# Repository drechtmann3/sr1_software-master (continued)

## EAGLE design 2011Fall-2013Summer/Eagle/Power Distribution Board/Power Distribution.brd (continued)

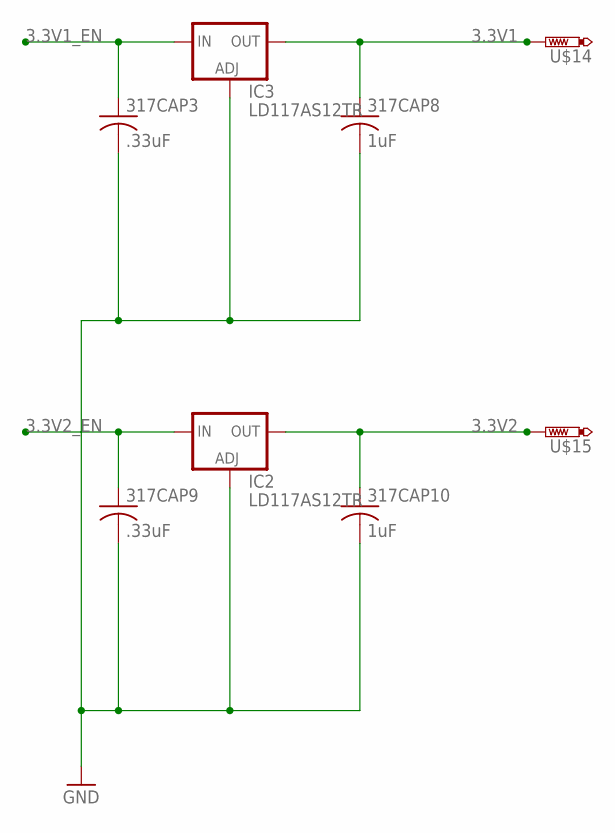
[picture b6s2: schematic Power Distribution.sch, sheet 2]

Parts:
317CAP3, 317CAP9: .33uF; C1206
317CAP8, 317CAP10: 1uF; C1206
IC2, IC3: LD117AS12TR; SOT223
U$14, U$15: TESTPAD-20MIL; 20MIL

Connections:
3.3V1: 317CAP8.1, IC3.4 (OUT), U$14.P$1; also elsewhere on the board
3.3V1_EN: 317CAP3.1, IC3.3 (IN); also elsewhere on the board
3.3V2: 317CAP10.1, IC2.4 (OUT), U$15.P$1; also elsewhere on the board
3.3V2_EN: 317CAP9.1, IC2.3 (IN); also elsewhere on the board
GND: 317CAP3.2, 317CAP8.2, 317CAP9.2, 317CAP10.2, IC2.1 (ADJ), IC3.1 (ADJ); also elsewhere on the board

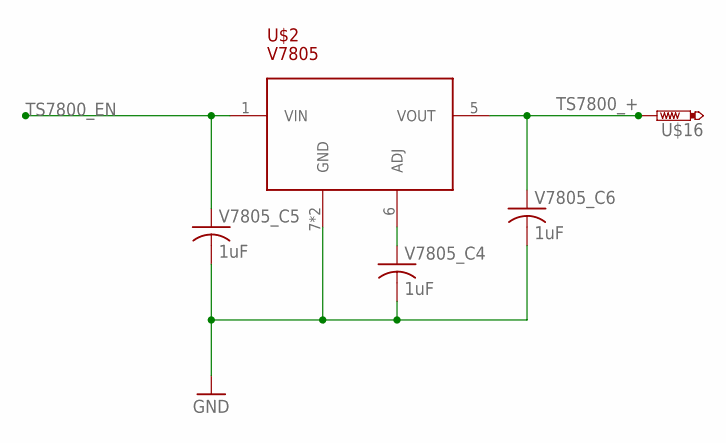
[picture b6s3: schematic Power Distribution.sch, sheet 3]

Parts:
U$2: V7805
U$16: TESTPAD-20MIL; 20MIL
V7805_C4, V7805_C5, V7805_C6: 1uF; C1206

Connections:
GND: U$2.7 (GND), U$2.9 (GND), V7805_C4.2, V7805_C5.2, V7805_C6.2; also elsewhere on the board
unnamed: U$2.6 (ADJ), V7805_C4.1
TS7800_+: U$2.5 (VOUT), U$16.P$1, V7805_C6.1; also elsewhere on the board
TS7800_EN: U$2.1 (VIN), V7805_C5.1; also elsewhere on the board

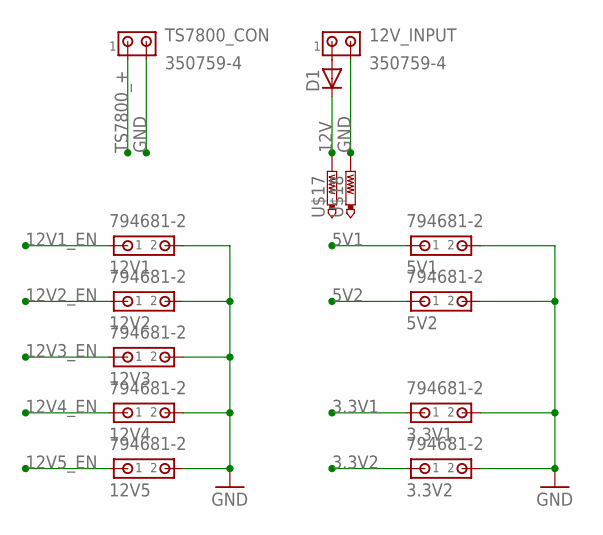
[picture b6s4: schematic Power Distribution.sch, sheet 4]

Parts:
3.3V1, 3.3V2, 5V1, 5V2, 12V1, 12V2, 12V3, 12V4, 12V5: 794681-2
12V_INPUT: 350759-4
D1: DIODE-SOD123; SOD123
TS7800_CON: 350759-4
U$17, U$18: TESTPAD-20MIL; 20MIL

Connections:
3.3V1: 3.3V1.1; also elsewhere on the board
3.3V2: 3.3V2.1; also elsewhere on the board
5V1: 5V1.1; also elsewhere on the board
5V2: 5V2.1; also elsewhere on the board
12V: D1.C, U$17.P$1; also elsewhere on the board
12V1_EN: 12V1.1; also elsewhere on the board
12V2_EN: 12V2.1; also elsewhere on the board
12V3_EN: 12V3.1; also elsewhere on the board
12V4_EN: 12V4.1; also elsewhere on the board
12V5_EN: 12V5.1; also elsewhere on the board
GND: 3.3V1.2, 3.3V2.2, 5V1.2, 5V2.2, 12V1.2, 12V2.2, 12V3.2, 12V4.2, 12V5.2, 12V_INPUT.2, TS7800_CON.2, U$18.P$1; also elsewhere on the board
unnamed: 12V_INPUT.1, D1.A
TS7800_+: TS7800_CON.1; also elsewhere on the board

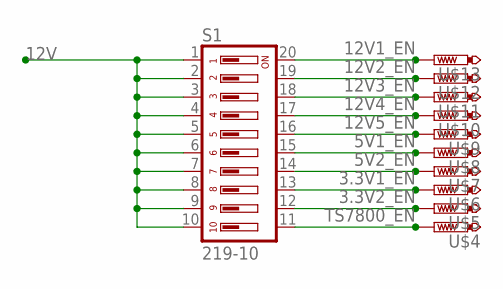
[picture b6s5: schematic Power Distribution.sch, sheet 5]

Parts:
S1: 219-10; CTS-219-10
U$4, U$5, U$6, U$7, U$8, U$9, U$10, U$11, U$12, U$13: TESTPAD-20MIL; 20MIL

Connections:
3.3V1_EN: S1.13, U$6.P$1; also elsewhere on the board
3.3V2_EN: S1.12, U$5.P$1; also elsewhere on the board
5V1_EN: S1.15, U$8.P$1; also elsewhere on the board
5V2_EN: S1.14, U$7.P$1; also elsewhere on the board
12V: S1.1, S1.2, S1.3, S1.4, S1.5, S1.6, S1.7, S1.8, S1.9, S1.10; also elsewhere on the board
12V1_EN: S1.20, U$13.P$1; also elsewhere on the board
12V2_EN: S1.19, U$12.P$1; also elsewhere on the board
12V3_EN: S1.18, U$11.P$1; also elsewhere on the board
12V4_EN: S1.17, U$10.P$1; also elsewhere on the board
12V5_EN: S1.16, U$9.P$1; also elsewhere on the board
TS7800_EN: S1.11, U$4.P$1; also elsewhere on the board

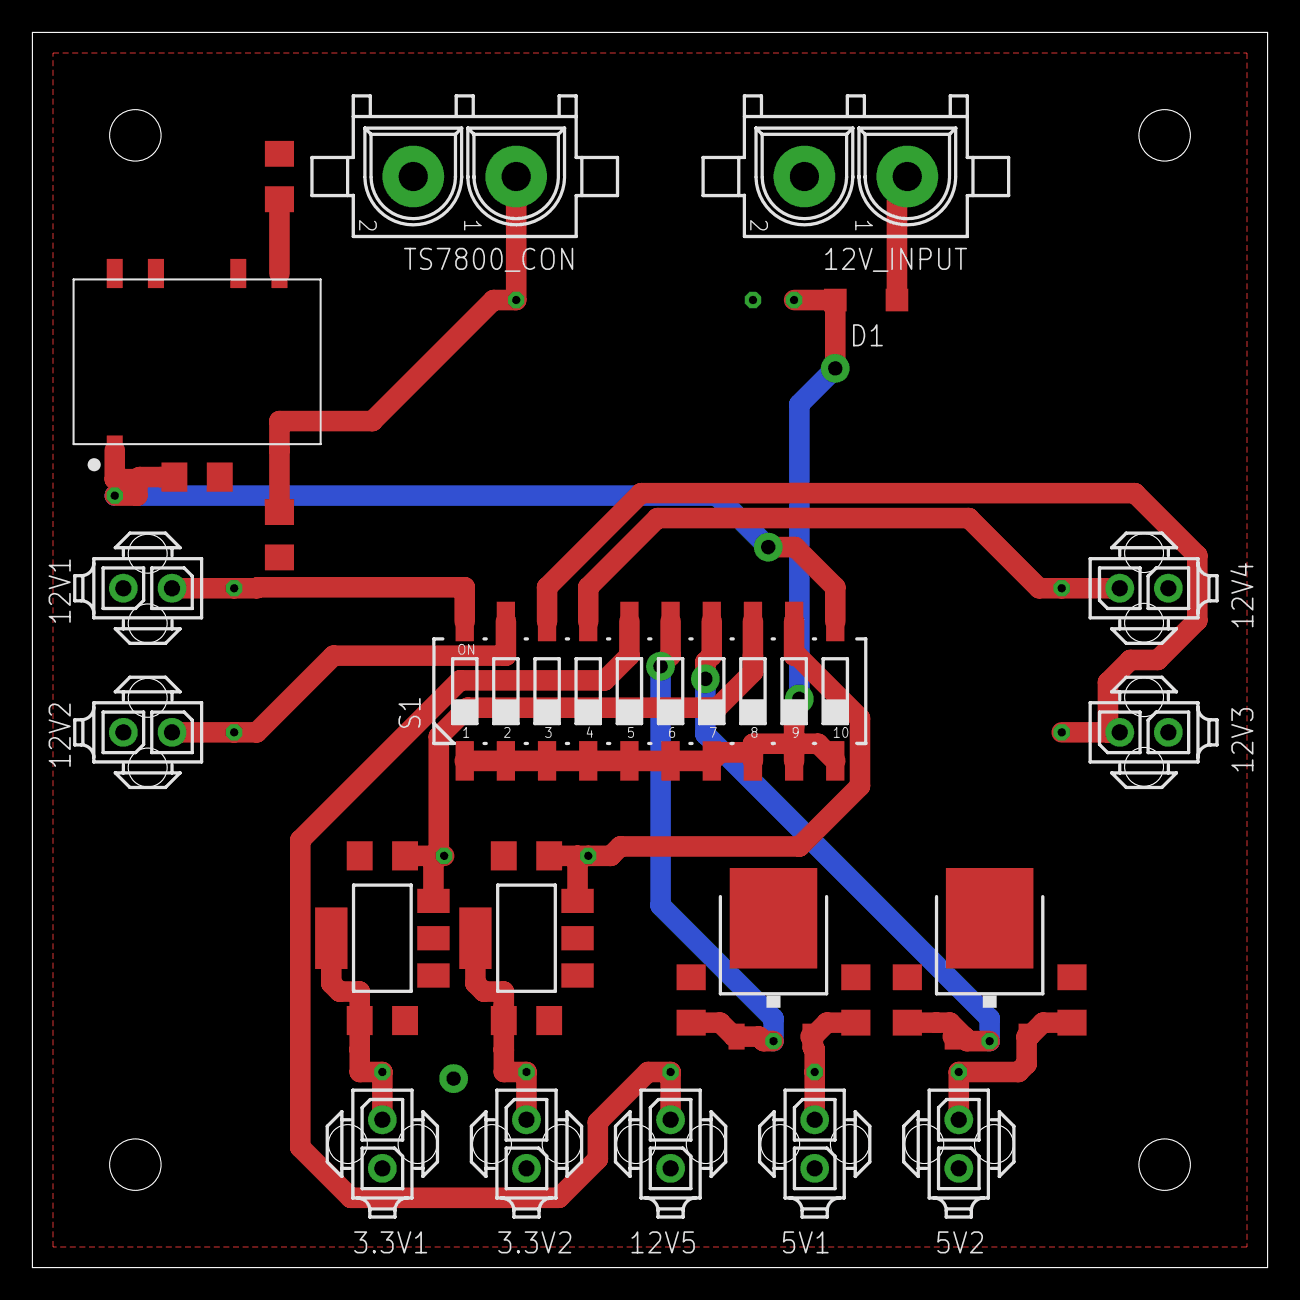
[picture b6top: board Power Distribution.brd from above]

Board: 2 copper layers, 76.2 x 76.2 mm, 46 parts (0 on the bottom side), 19 nets.

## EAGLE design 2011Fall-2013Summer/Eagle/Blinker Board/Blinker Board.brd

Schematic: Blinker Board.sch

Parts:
12V: TESTPAD-20MIL; 20MIL
B: TESTPAD-20MIL; 20MIL
BC: TESTPAD-20MIL; 20MIL
BL: TESTPAD-20MIL; 20MIL
BLC: TESTPAD-20MIL; 20MIL
BLINKER-L1, BLINKER-L2: PMV56XN215; SOT23
BLINKER-R1, BLINKER-R2: PMV56XN215; SOT23
BLLB: TESTPAD-20MIL; 20MIL
BLLF: TESTPAD-20MIL; 20MIL
BLRB: TESTPAD-20MIL; 20MIL
BLRF: TESTPAD-20MIL; 20MIL
BR: TESTPAD-20MIL; 20MIL
BRAKE-C1: N-CHANNEL_MOSFETPMV56XN,215; SOT23; PART_NUM PMV56XN,215
BRAKE-L1: PMV56XN215; SOT23; PART_NUM PMV56XN,215
BRAKE-R1: PMV56XN215; SOT23
BRC: TESTPAD-20MIL; 20MIL
GND: TESTPAD-20MIL; 20MIL
J1: 794681-2
R1, R3, R5, R6, R7, R9, R10, R14, R15, R16: 1k; R1206; PART_NUM CR1206-FX-1001GLF
U$1: AMP_LATCH_14; MA14-2
X1: C-GRID-03-70553; 70553-03

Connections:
12V: 12V.P$1, J1.1, U$1.1 (7), U$1.3 (9), U$1.5 (11), U$1.7 (13), U$1.9 (15), U$1.11 (17), U$1.13 (19)
BLINKER_L: BLC.P$1, BLINKER-L1.1 (G), BLINKER-L2.1 (G), R5.2, R6.2, R10.2
BLINKER_L_BACK_-: BLINKER-L2.3 (D), BLLB.P$1, U$1.6 (12)
BLINKER_L_FRONT_-: BLINKER-L1.3 (D), BLLF.P$1, U$1.8 (14)
BLINKER_R: BLINKER-R1.1 (G), BLINKER-R2.1 (G), BRC.P$1, R7.1, R14.2, R15.2
BLINKER_R_BACK_-: BLINKER-R2.3 (D), BLRB.P$1, U$1.2 (8)
BLINKER_R_FRONT_-: BLINKER-R1.3 (D), BLRF.P$1, U$1.4 (10)
BRAKE: B.P$1, BRAKE-C1.1 (G), BRAKE-L1.1 (G), BRAKE-R1.1 (G), R1.2, R3.2, R9.2, R16.2
BRAKE_C_-: BC.P$1, BRAKE-C1.3 (D), U$1.12 (18)
BRAKE_L_-: BL.P$1, BRAKE-L1.3 (D), U$1.10 (16)
BRAKE_R_-: BR.P$1, BRAKE-R1.3 (D), U$1.14 (20)
GND: BLINKER-L1.2 (S), BLINKER-L2.2 (S), BLINKER-R1.2 (S), BLINKER-R2.2 (S), BRAKE-C1.2 (S), BRAKE-L1.2 (S), BRAKE-R1.2 (S), GND.P$1, J1.2, R1.1, R3.1, R5.1, R6.1, R14.1, R15.1, R16.1
unnamed: R7.2, X1.1
unnamed: R10.1, X1.2
unnamed: R9.1, X1.3

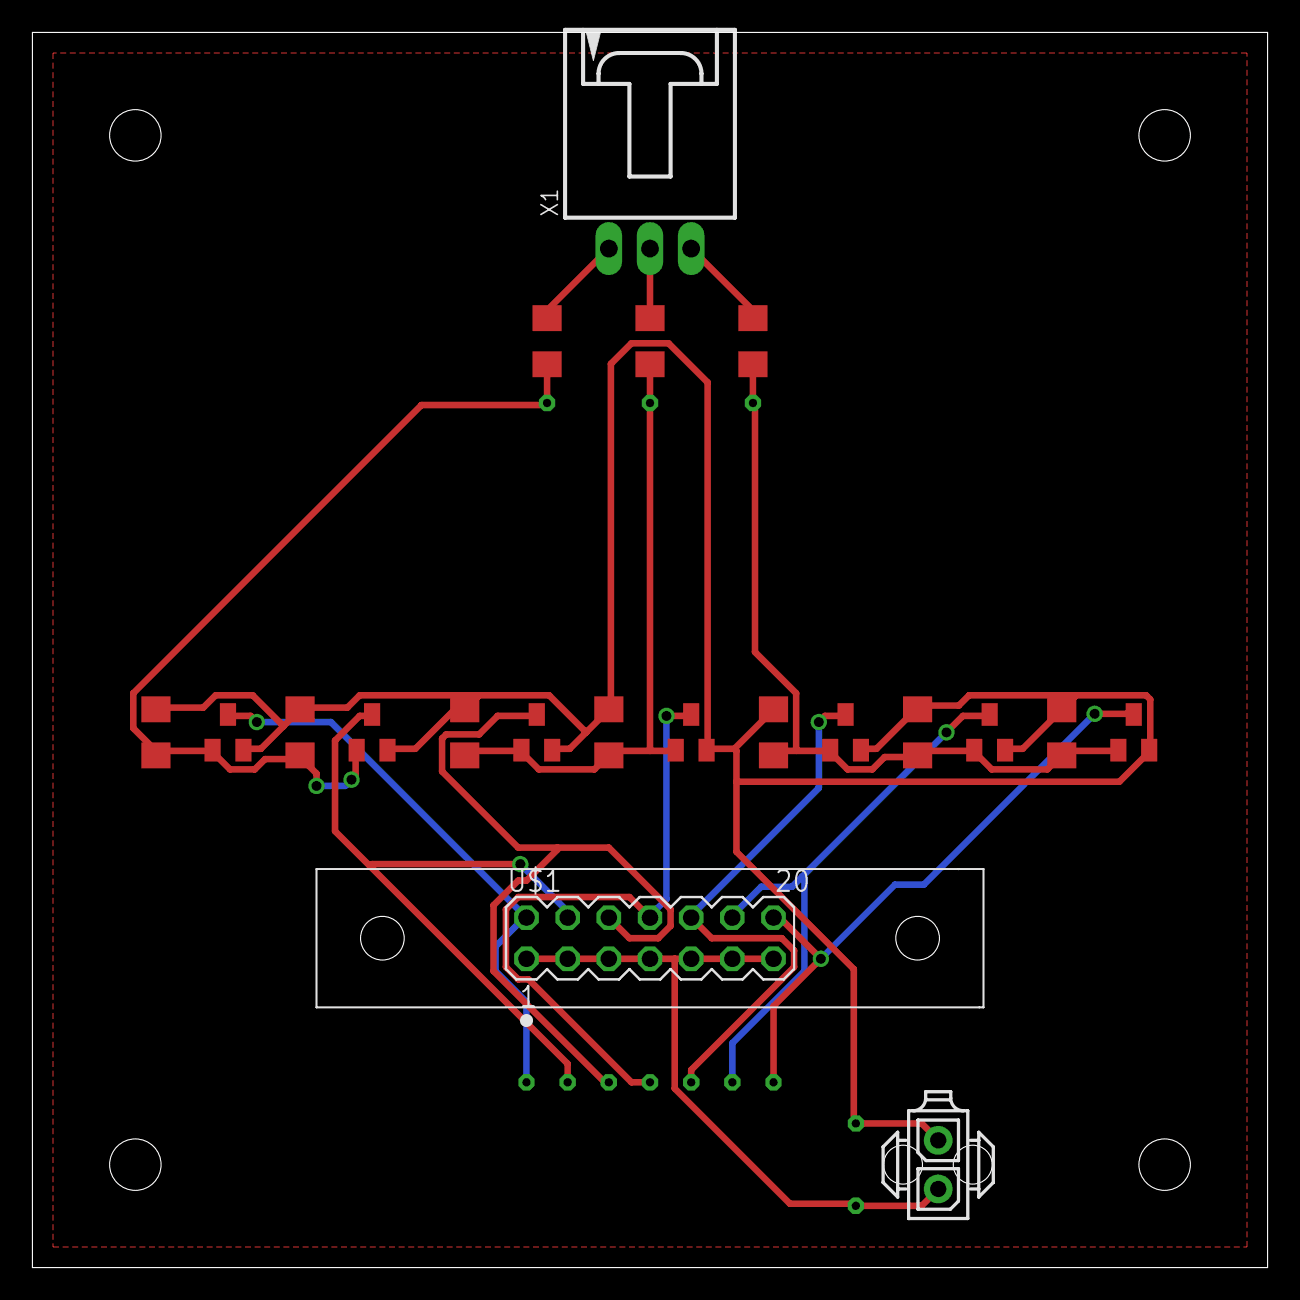
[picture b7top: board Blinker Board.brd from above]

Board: 2 copper layers, 76.2 x 76.2 mm, 32 parts (0 on the bottom side), 15 nets.

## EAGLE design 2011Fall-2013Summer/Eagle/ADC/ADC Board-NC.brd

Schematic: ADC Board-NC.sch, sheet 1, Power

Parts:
3.3V_TP, 5V_TP, 12V: TESTPAD-20MIL; 20MIL
5V: LM7805TV; TO252
5VREF: MAX6105; SOT23
317CAP1, 317CAP2, 6103CAP1, 6103CAP2, 7805CAP2: 1uF; C1206
7805CAP1: .33uF; C1206
AGND: TESTPAD-20MIL; 20MIL
GND: TESTPAD-20MIL; 20MIL
IC1: LD117AS12TR; SOT223
R1: 0; R1206
VREF_TP: TESTPAD-20MIL; 20MIL

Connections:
3.3V: 3.3V_TP.P$1, 317CAP2.1, IC1.4 (OUT)
5V: 5V.2 (VO), 5V_TP.P$1, 7805CAP2.1; also elsewhere on the board
12V: 5V.1 (VI), 5VREF.1 (IN), 12V.P$1, 317CAP1.1, 6103CAP1.1, 7805CAP1.1, IC1.3 (IN); also elsewhere on the board
AGND: 5VREF.3 (GND), 6103CAP1.2, 6103CAP2.2, AGND.P$1, R1.2; also elsewhere on the board
GND: 5V.3 (GND), 317CAP1.2, 317CAP2.2, 7805CAP1.2, 7805CAP2.2, GND.P$1, IC1.1 (ADJ), R1.1; also elsewhere on the board
VREF: 5VREF.2 (OUT), 6103CAP2.1, VREF_TP.P$1; also elsewhere on the board

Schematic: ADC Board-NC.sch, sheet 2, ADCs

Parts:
ADC1: MCP-3008; SO16
ADC_CAP1: .1uF; C1206
IN1, IN2, IN3, IN4, IN5, IN6, IN7, IN8: TESTPAD-20MIL; 20MIL
SPI_CLK: TESTPAD-20MIL; 20MIL
SPI_CS1: TESTPAD-20MIL; 20MIL
SPI_DIN: TESTPAD-20MIL; 20MIL
SPI_DOUT: TESTPAD-20MIL; 20MIL

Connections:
5V: ADC1.16 (VDD), ADC_CAP1.1; also elsewhere on the board
AGND: ADC1.14 (AGND); also elsewhere on the board
GND: ADC1.9 (DGND), ADC_CAP1.2; also elsewhere on the board
IN1: ADC1.1 (CH0), IN1.P$1; also elsewhere on the board
IN2: ADC1.2 (CH1), IN2.P$1; also elsewhere on the board
IN3: ADC1.3 (CH2), IN3.P$1; also elsewhere on the board
IN4: ADC1.4 (CH3), IN4.P$1; also elsewhere on the board
IN5: ADC1.5 (CH4), IN5.P$1; also elsewhere on the board
IN6: ADC1.6 (CH5), IN6.P$1; also elsewhere on the board
IN7: ADC1.7 (CH6), IN7.P$1; also elsewhere on the board
IN8: ADC1.8 (CH7), IN8.P$1; also elsewhere on the board
SPI_CLK: ADC1.13 (CLK), SPI_CLK.P$1; also elsewhere on the board
SPI_CS1: ADC1.10 (CS), SPI_CS1.P$1; also elsewhere on the board
SPI_DIN: ADC1.11 (DIN), SPI_DIN.P$1; also elsewhere on the board
SPI_DOUT: ADC1.12 (DOUT), SPI_DOUT.P$1; also elsewhere on the board
VREF: ADC1.15 (VREF); also elsewhere on the board

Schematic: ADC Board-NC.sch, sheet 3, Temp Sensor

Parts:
U$2: LM35; SO-08

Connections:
12V: U$2.8 (V+); also elsewhere on the board
AGND: U$2.4 (GND); also elsewhere on the board
IN8: U$2.1 (OUT); also elsewhere on the board

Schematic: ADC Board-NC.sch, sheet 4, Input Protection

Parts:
U$6: SP720APP; SO16

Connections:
AGND: U$6.8 (V-); also elsewhere on the board
IN1: U$6.1 (IN1); also elsewhere on the board
IN2: U$6.2 (IN2); also elsewhere on the board
IN3: U$6.3 (IN3); also elsewhere on the board
IN4: U$6.4 (IN4); also elsewhere on the board
IN5: U$6.5 (IN5); also elsewhere on the board
IN6: U$6.6 (IN6); also elsewhere on the board
IN7: U$6.7 (IN7); also elsewhere on the board
IN8: U$6.9 (IN9); also elsewhere on the board
VREF: U$6.16 (V+); also elsewhere on the board

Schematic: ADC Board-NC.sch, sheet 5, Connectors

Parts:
J1: 794681-2
U$1: AMP_LATCH_22; MA22-2
X1: C-GRID-04-70553; 70553-04

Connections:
12V: J1.1; also elsewhere on the board
AGND: U$1.3, U$1.6, U$1.9, U$1.12, U$1.15, U$1.18, U$1.21; also elsewhere on the board
GND: J1.2; also elsewhere on the board
IN1: U$1.1; also elsewhere on the board
IN2: U$1.4; also elsewhere on the board
IN3: U$1.7; also elsewhere on the board
IN4: U$1.10; also elsewhere on the board
IN5: U$1.13; also elsewhere on the board
IN6: U$1.16; also elsewhere on the board
IN7: U$1.19; also elsewhere on the board
SPI_CLK: X1.1; also elsewhere on the board
SPI_CS1: X1.4; also elsewhere on the board
SPI_DIN: X1.3; also elsewhere on the board
SPI_DOUT: X1.2; also elsewhere on the board
VREF: U$1.2, U$1.5, U$1.8, U$1.11, U$1.14, U$1.17, U$1.20; also elsewhere on the board

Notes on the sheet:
Schrödinger Cable 3.5ft #12 stranded cable

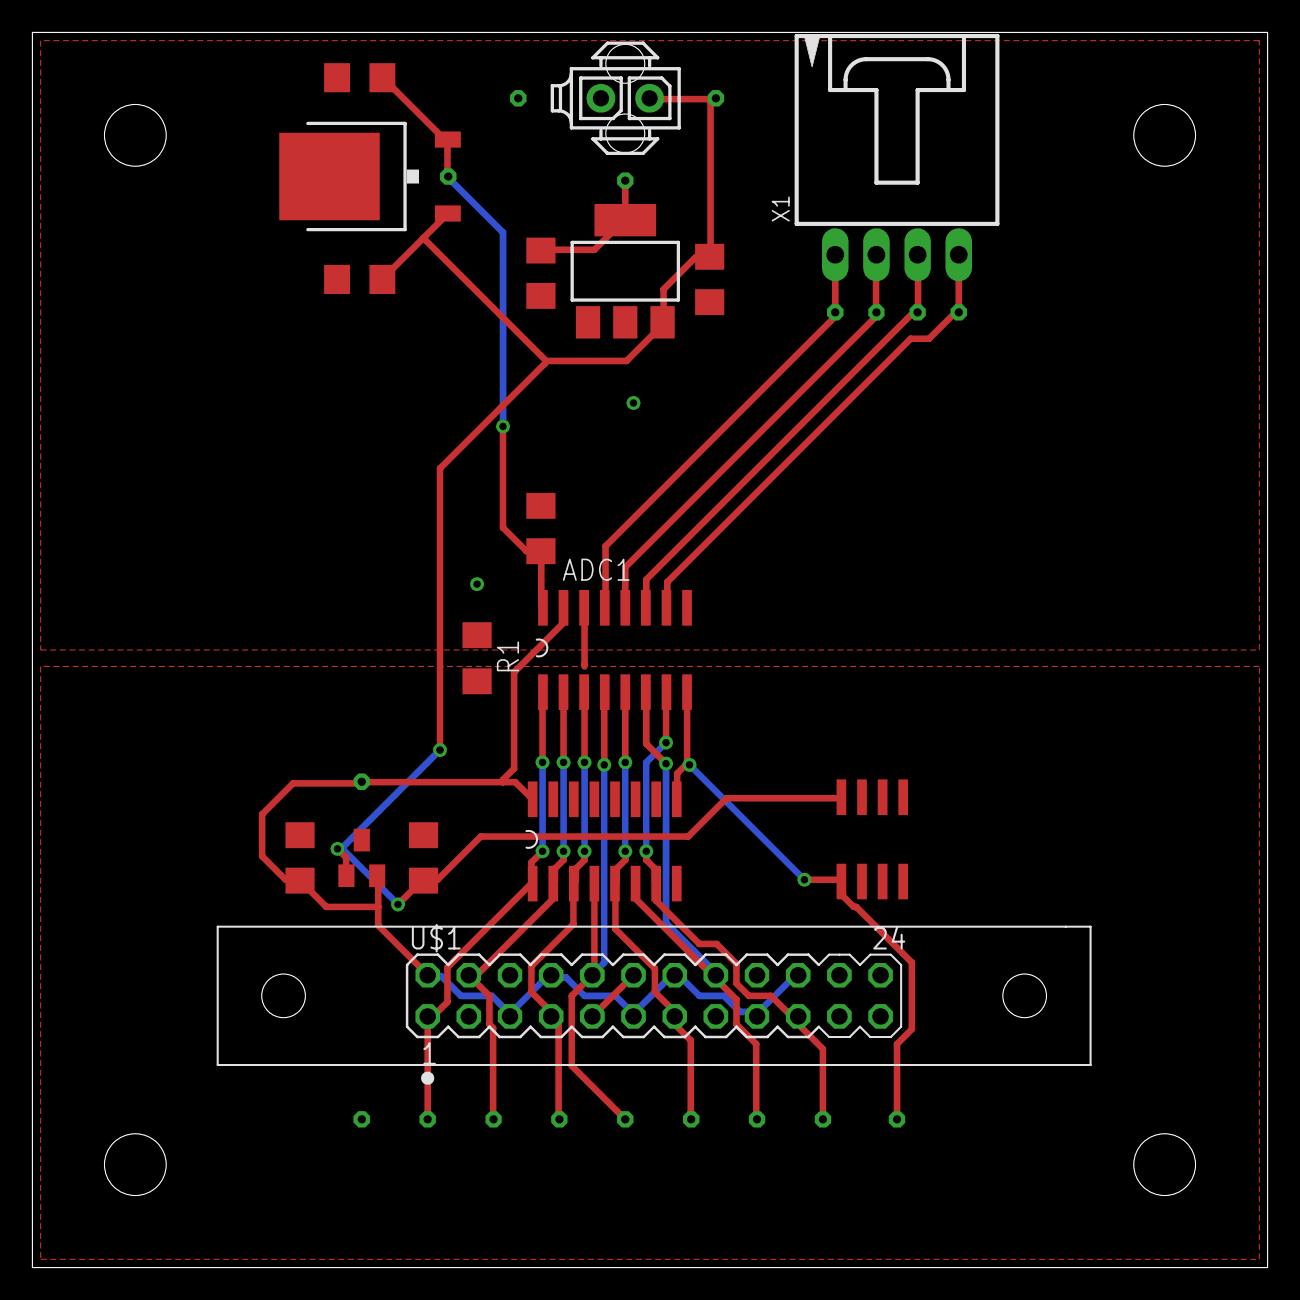
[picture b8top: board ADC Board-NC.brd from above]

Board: 2 copper layers, 76.2 x 76.2 mm, 35 parts (0 on the bottom side), 18 nets.

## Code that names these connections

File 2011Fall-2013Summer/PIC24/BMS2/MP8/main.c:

//Files to be included
#include "main.h"
#include "ADC.h"
#include "ltc.h"
#include "relay.h"
//System Files
#include <p24HJ128GP202.h>
#include <stdint.h>        /* Includes uint16_t definition                    */
#include <stdbool.h>       /* Includes true/false definition                  */


int16_t main(void)
{
	//TODO discharge calculations
	int i = LTC3;
	int j;
	char voltages[19];
	int selfCheck = 0;

	configPins();
	configClock();
	

	//Comment out next 5 lines if debugging
	selfCheck += initLTC();
	selfCheck += initADC();//initADC();
	if(selfCheck == 2){
		setRelay(RELAY_ON);
	}

    while(1)
    {	
		//comment out next 4 lines if debugging
		for(i = LTC1; i < LTC_ALL; i++){
			LTC_readVoltages(i);
		}
		checkADC();


		//uncomment next 0 lines if debugging RS-485
		
		//unComment next 3 lines if debugging LTC
		//LTC_writeConfig(LTC_ALL, 0);
		//LTC_readVoltages(i);
		//LTC_analyzeVolts(i);

		//uncomment out next 3 lines if debugging ADC
//		j = ADCReadRaw(TEMP1_CHANNEL);
//		j++;
//		j--;
	}
}

void configPins(){

	AD1PCFGL = 0b1111111111111111; //set all bits not to be analog

	//TRISx defines the input/output state of pins. 1 represents input, while 0 represents output.
	TRISAbits.TRISA0 = 0;	// warn1
	TRISAbits.TRISA1 = 0;	// warn2 
	TRISAbits.TRISA3 = 0;	// Critical
	TRISAbits.TRISA4 = 0;	// DI/RO
	
	TRISBbits.TRISB2 = 0;	//MOSI
	TRISBbits.TRISB3 = 0;	//SCK
	TRISBbits.TRISB4 = 0;	//Relay
	TRISBbits.TRISB5 = 1;	//MISO LTC1
	TRISBbits.TRISB6 = 1;	//MISO LTC2	
	TRISBbits.TRISB7 = 1;	//MISO LTC3
	TRISBbits.TRISB8 = 1;	//MISO ADC
	TRISBbits.TRISB9 = 1;	//RX    
	TRISBbits.TRISB10 = 0;	//TX
	TRISBbits.TRISB11 = 0;	//FAULT
	TRISBbits.TRISB12 = 0;	//CS LTC1
	TRISBbits.TRISB13 = 0;	//CS LTC2
	TRISBbits.TRISB14 = 0;	//CS LTC3
	TRISBbits.TRISB15 = 0;	//CS ADC


	LATBbits.LATB3 = 0; //SET CLOCK LOW
	setRelay(RELAY_OFF); //make sure the relay is off
	LATAbits.LATA0 = 0; //set warn1 off
	LATAbits.LATA1 = 0; //set warn2 off
	LATAbits.LATA3 = 0; //set critical led off
	LATBbits.LATB12 = 1;
	LATBbits.LATB13 = 1;
	LATBbits.LATB14 = 1;
}

void configClock() {
        // Clock scaling settings
        CLKDIVbits.DOZEN = 0;                   // 0 = Processor clock/peripheral clock ratio forced to 1:1
        CLKDIVbits.PLLPRE = 0b0;                // PLL pre divider, 0b0 = 2
        CLKDIVbits.PLLPOST = 0b1;               // PLL post divider, 0b1 = 4
        PLLFBDbits.PLLDIV = 0b110000;   // PLL multipler (even though called "divider"), 0b110000 = 50 (default)

}

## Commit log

2015-04-11 :circus_tent: Added .gitattributes & .gitignore files
2015-04-18 added 2 files
    merged two folders, so project.c and project.h is in the right Project
    libraries folder
2015-04-18 CZSC
    c and h
